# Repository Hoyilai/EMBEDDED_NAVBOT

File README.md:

# EMBEDDED_NAVBOT

•	Embedded System Design: Designed and fabricated an extended board and circuit with SMD-sized components such as LED, resistors, capacitors, IR sensors, LSM9DS1 IMU, and motor devices for a robot cart. 

•	Developed a versatile navigation system utilizing sensor and camera input, with capabilities for remote control, autodrive, and following traces or laser guidance.

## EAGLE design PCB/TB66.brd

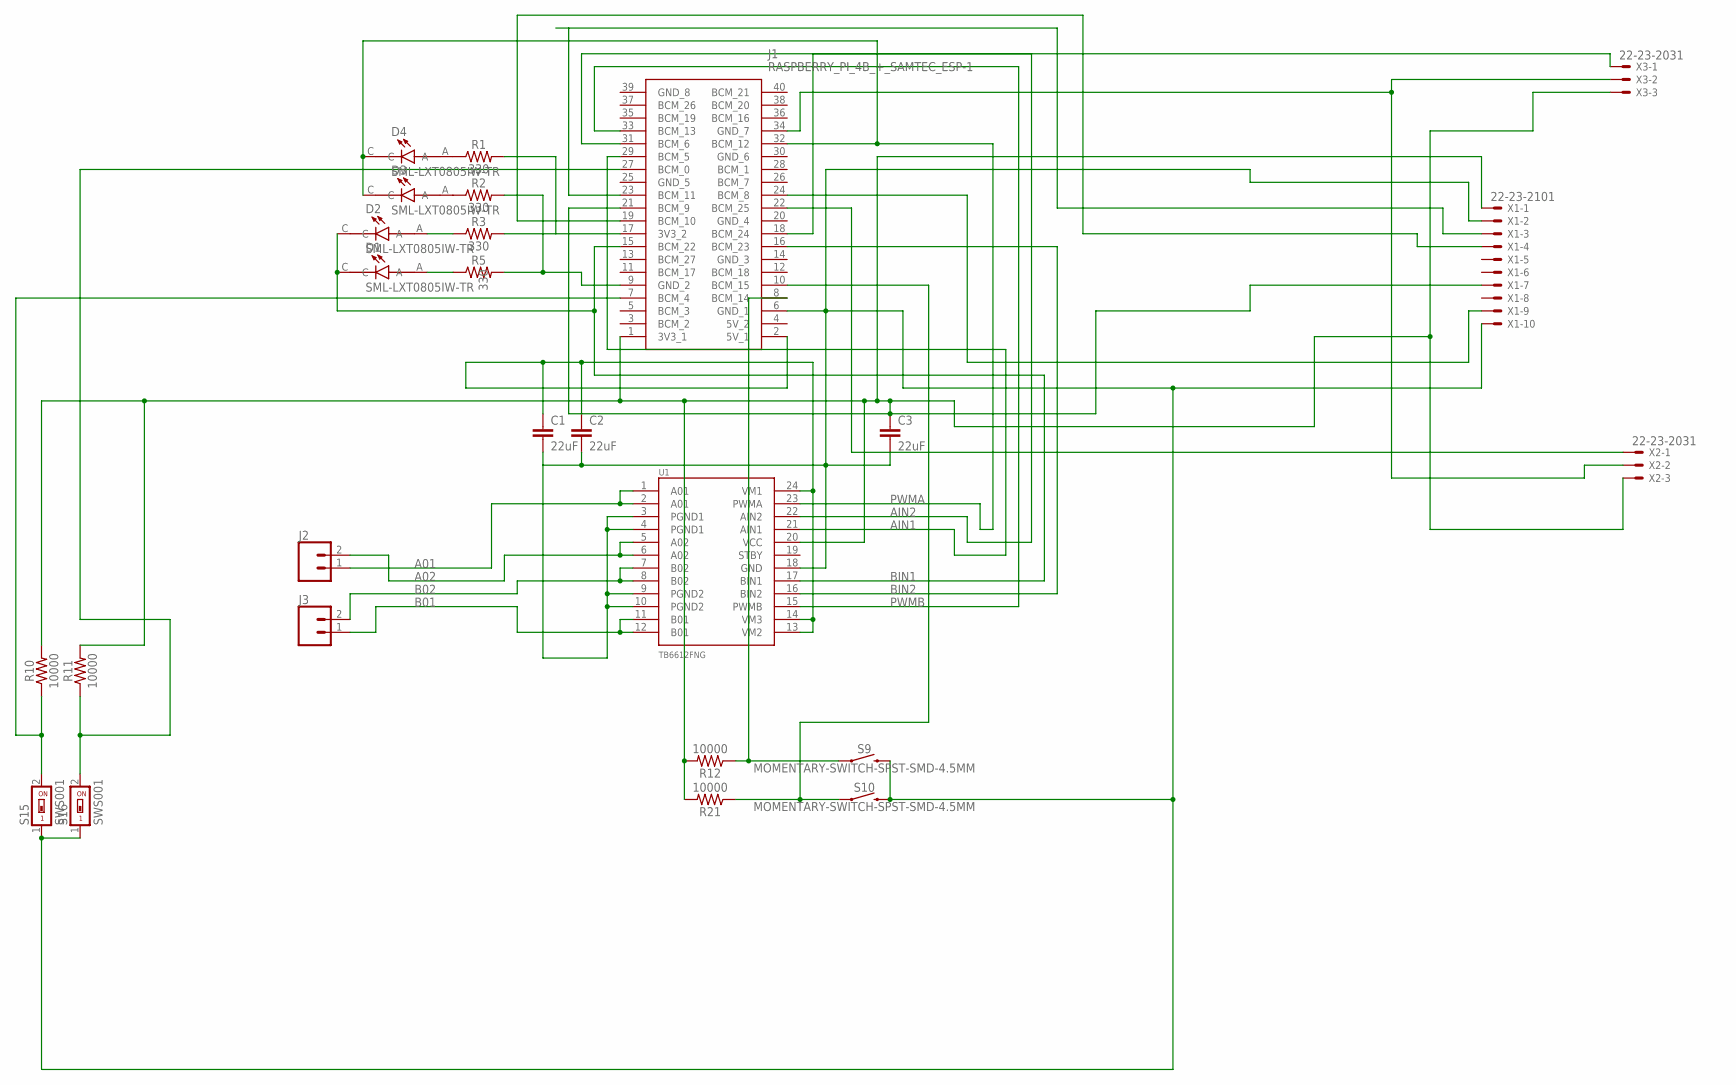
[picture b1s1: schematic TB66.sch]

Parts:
C1, C2, C3: 22uF; 0805
D1, D2, D3, D4: SML-LXT0805IW-TR; LEDC2012X120N
J1: RASPBERRY_PI_4B_+_SAMTEC_ESP-1; RASPBERRYPI4B4GB
J2, J3: CONN_023.5MM; SCREWTERMINAL-3.5MM-2
R1, R2, R3, R5: 330; 0805
R10, R11, R12, R21: 10000; 0805
S9, S10: MOMENTARY-SWITCH-SPST-SMD-4.5MM; TACTILE_SWITCH_SMD_4.5MM
S15, S16: SWS001; SMS-001
U1: TB6612FNG; SSOP24
X1: 22-23-2101
X2, X3: 22-23-2031

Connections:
5V_2: J1.4 (5V_2)
A01: J2.1, U1.1 (A01), U1.2 (A01)
A02: J2.2, U1.5 (A02), U1.6 (A02)
AIN1: J1.29 (BCM_5), U1.21 (AIN1)
AIN2: J1.31 (BCM_6), U1.22 (AIN2)
B01: J3.1, U1.11 (B01), U1.12 (B01)
B02: J3.2, U1.7 (B02), U1.8 (B02)
BIN1: D1.C, D2.C, J1.15 (BCM_22), U1.17 (BIN1)
BIN2: J1.16 (BCM_23), U1.16 (BIN2)
GND_3: J1.14 (GND_3)
GND_4: J1.20 (GND_4)
GND_5: J1.25 (GND_5)
GND_6: J1.30 (GND_6)
GND_8: J1.39 (GND_8)
unnamed: D3.A, R2.1
unnamed: J1.34 (GND_7), X2.2, X3.2
unnamed: C1.2, C2.2, C3.2, J1.6 (GND_1), S9.1 (2), S9.4 (2), S10.1 (2), S10.4 (2), S15.1, S16.1, U1.3 (PGND1), U1.4 (PGND1), U1.9 (PGND2), U1.10 (PGND2), U1.18 (GND), X1.2, X1.10
unnamed: J1.17 (3V3_2), R1.2, R3.2
unnamed: D4.A, R1.1
unnamed: D1.A, R5.1
unnamed: J1.9 (GND_2), R2.2, R5.2
unnamed: D2.A, R3.1
unnamed: J1.18 (BCM_24), X3.1
unnamed: J1.23 (BCM_11), X1.3
unnamed: J1.19 (BCM_10), X1.4
unnamed: C3.1, J1.1 (3V3_1), J1.21 (BCM_9), R10.2, R11.2, R12.2, R21.2, U1.20 (VCC), X1.1, X1.7, X2.3, X3.3
unnamed: J1.24 (BCM_8), X1.9
unnamed: J1.22 (BCM_25), X2.1
unnamed: J1.8 (BCM_14), R12.1, S9.2 (1), S9.3 (1)
unnamed: J1.10 (BCM_15), R21.1, S10.2 (1), S10.3 (1)
unnamed: J1.7 (BCM_4), R10.1, S15.2
unnamed: J1.27 (BCM_0), R11.1, S16.2
PWMA: D3.C, D4.C, J1.32 (BCM_12), U1.23 (PWMA)
PWMB: J1.33 (BCM_13), U1.15 (PWMB)
VM: C1.1, C2.1, J1.2 (5V_1), U1.13 (VM2), U1.14 (VM3), U1.24 (VM1)

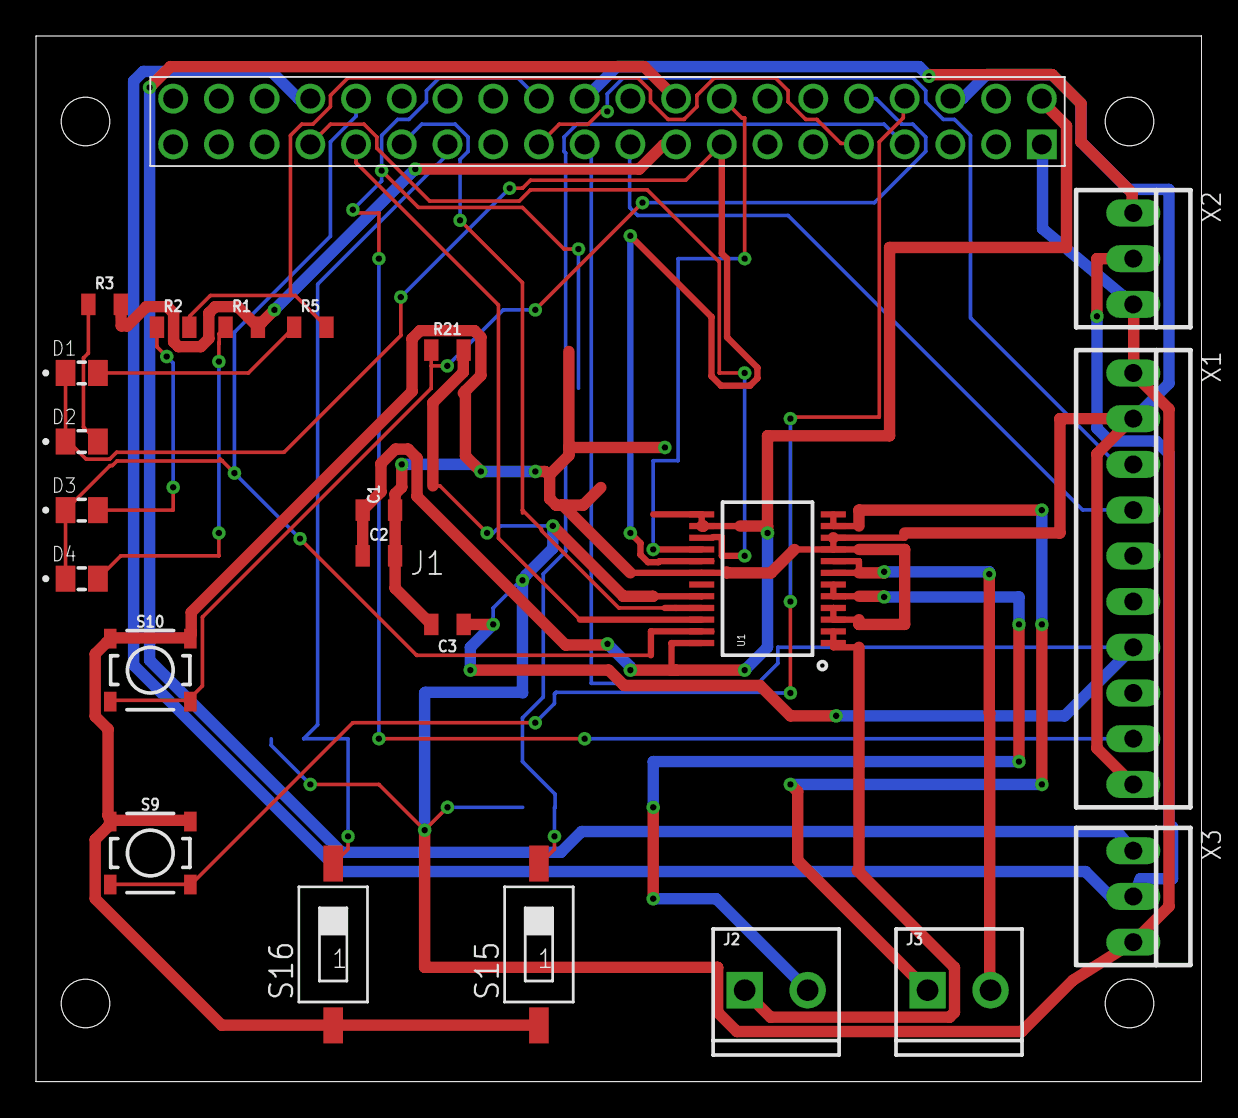
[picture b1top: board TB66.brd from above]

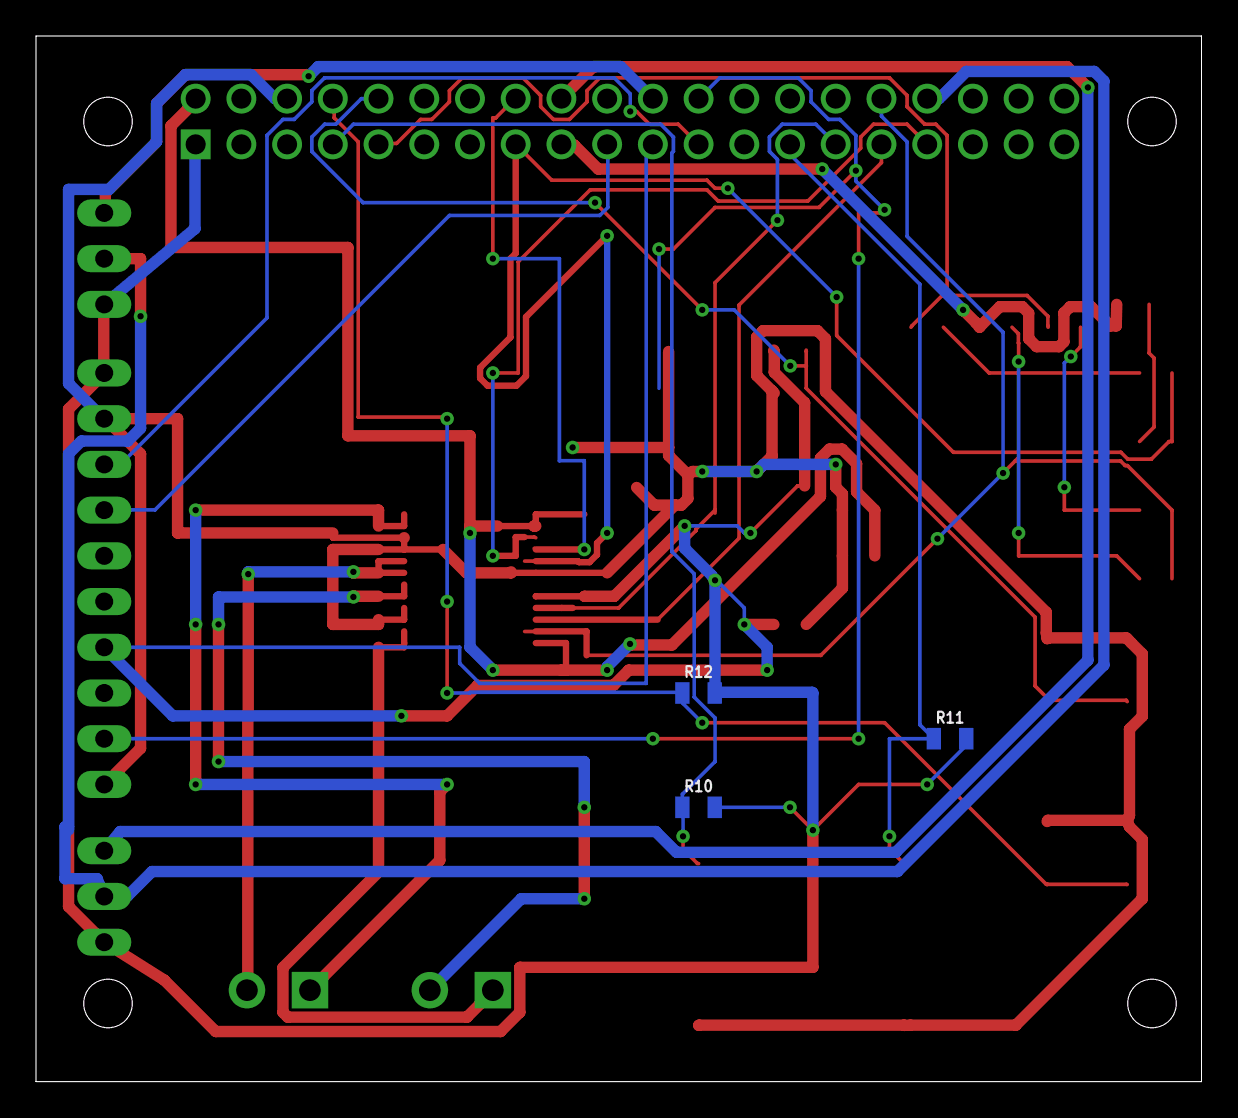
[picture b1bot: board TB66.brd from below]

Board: 2 copper layers, 64.8 x 58.1 mm, 26 parts (3 on the bottom side), 29 nets.

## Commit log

2023-08-15 update of the code
2023-08-15 PCB_Update

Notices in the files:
parts and their libraries:
SparkFun-Connectors: Licensing: Creative Commons ShareAlike 4.0 International - https://creativecommons.org/licenses/by-sa/4.0
